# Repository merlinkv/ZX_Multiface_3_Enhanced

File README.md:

# ZX Multiface 3 Enhanced

<br />This work is licensed under a <a rel="license" href="http://creativecommons.org/licenses/by-nc-sa/4.0/">Creative Commons Attribution-NonCommercial-ShareAlike 4.0 International License</a>.

* If you remix, transform, or build upon the material, you must distribute your contributions under the same license as the original.
* You may not use the material for commercial purposes.
* You must give appropriate credit, provide a link to the license, and indicate if changes were made. You may do so in any reasonable manner, but not in any way that suggests the licensor endorses you or your use.

This interface is based on the Multiface 3 clone by Hard Micro and the recreation made by José Leandro Novellón.

# ATTENTION

   - This project was made for retro community, individuals or forums, and NOT FOR COMMERCIAL PURPOSES.
   - Its commercial sale on eBay, auction sites or shops (online or not) is PROHIBITED.
   - So only retro hardware forums and individual people with non profit intentions can build this project.

# Exception

  - If you wish to sell small quantities of this interface in a physical or online store, you must first contact me to request permission. The ban on selling it on eBay or auction sites remains in effect.

**I take no responsibiltiy for any damage to any equipment that results from the use of this board.**

USE IT AT YOUR OWN RISK!

# Version 2.0s - September 2, 2024

- Added case files of version 2.0s (STL - 3D Printer files)

# Version 2.0Ds - August 15, 2024

- New version of the board. This is an small form factor PCB but including a rear Edge connector.
- To maintain the size, the board has been designed as a four layers PCB.
- [Interactive BOM](https://htmlpreview.github.io/?https://github.com/merlinkv/ZX_Multiface_3_Enhanced/blob/main/ZX_Multiface_3_2_0Ds.html)

# Version 2.0s Final - August 6, 2024

- Version 2.0s has been tested an working 100%
- [Interactive BOM](https://htmlpreview.github.io/?https://github.com/merlinkv/ZX_Multiface_3_Enhanced/blob/main/ZX_Multiface_3_2_0s.html)

# Added version 2.0s (small) - July 04, 2024 - RC2 version, needs to be tested.

   - Redefined Kempston Joystick side (no more GAL22V10D)
   - Stay only three TH components 27E257 (ROMs), 6264/62256 (RAM) and GAL16V8B (MF3 operative) all other componentes now are SMD/SMT.
   - PCB size: 73.1 x 86.3 mm

# Versions 1.5D & 1.5DE - August 12, 2021

A better routing of the boards has been carried out and a power LED has been added.

Version 1.5DE has a rear expansion port.

# Version 1.4D - December 1, 2020

Started in April 2020, I finally got the expected results and created a fully operational and enhanced clone
of the Romantic Robot Multiface 3 for ZX Spectrum +3 computers.

The following project is a modified and improved version of the Multiface 3 interface originally designed by Romantic Robot UK LTD.
The Spanish company Hard Micro made, back in 1988, a clone of the Multiface 3. Since then there have been no more recreations that I know of.

The Multiface 3 is a multipurpose interface designed for ZX Spectrum +3 computers that, among many other functionalities,
allows us to make backup copies of programs or games on tape or disk. If used on the + 2A / + 2B models, such copies can only be made on tape.

The main changes compared to the original model are:

- Dual ROM based on a W27E257
- PAL16L8 replaced by GAL16V8B
- RAM 6264 or 62256 (best to use HM62256ALP-10).
- Tested RAM IC's:
  - HM62256ALP-10
  - HM6264LP-12
  - HY62256A LP-70
  - UT6264CPCL-70LL 
- RESET button.
- Decoupling capacitors for all IC's.
- Horizontal EDGE connector.
- PCB designed to put inside a printed 3D case.
- Kempston Joystick interface (can be enabled or disabled)

# Notes for Gotek (FlashFloppy) users:

- To format a real 3.5" disk to 720k that the ZX +3 can read (+3DOS), the best is to do it with the CPCDiskXP utility.
- These DSK files can be used as real diks to save or load MF3 snapshots.
- You must update the Gotek firmware to the latest FlashFloppy version (at the moment the v3.42).

# General Notes

- All versions, **1.4D, 1.5D, 1.5DE & 2.0s & 2.0Ds** have been tested on my ZX +3 computers and are working perfectly even with the +3e ROMs by Garry Lancaster (https://worldofspectrum.org/zxplus3e/)

# Links:

- https://www.winuaespanol.com/phpbb3/viewtopic.php?p=5981#p5981
- https://hardware.speccy.org/old.html
- https://k1.spdns.de/Vintage/Sinclair/82/Peripherals/Multiface%20I%2C%20128%2C%20and%20%2B3%20(Romantic%20Robot)/MF3/Technical%20Information/
- https://speccy4ever.speccy.org/_RR.htm

Special thanks to José Leandro, Bone and Cacharreo for their help.

# Contact

You can contact with me at the next forums:

- https://www.winuaespanol.com/phpbb3/index.php
- https://www.va-de-retro.com/foros/index.php
- http://retrowiki.es/portal

# Original introduction

MULTIFACE 3 is a multi-purpose interface designed exclusively for the
SPECTRUM+3. It provides fully automatic and universal back-up/transfer of
48/128K programs from tape to disk, disk to tape, tape to tape and disk to
disk. It also incorporates a comprehensive toolkit enabling you to
study/modify/develop software. MULTIFACE 3 can copy screens to printer in
hi-res modes and it extends the use of DOS in 48 SPECTRUM mode. MULTIFACE
is menu-driven, fully error-trapped with on-screen prompts and it largely
uses a system of one-touch commands. It is very easy to use and does not
really need a separate written manual. Nonetheless, the following few pages
should help you to understand every aspect of MULTIFACE 3 operations so that
you can use it to its fullest possible potential.

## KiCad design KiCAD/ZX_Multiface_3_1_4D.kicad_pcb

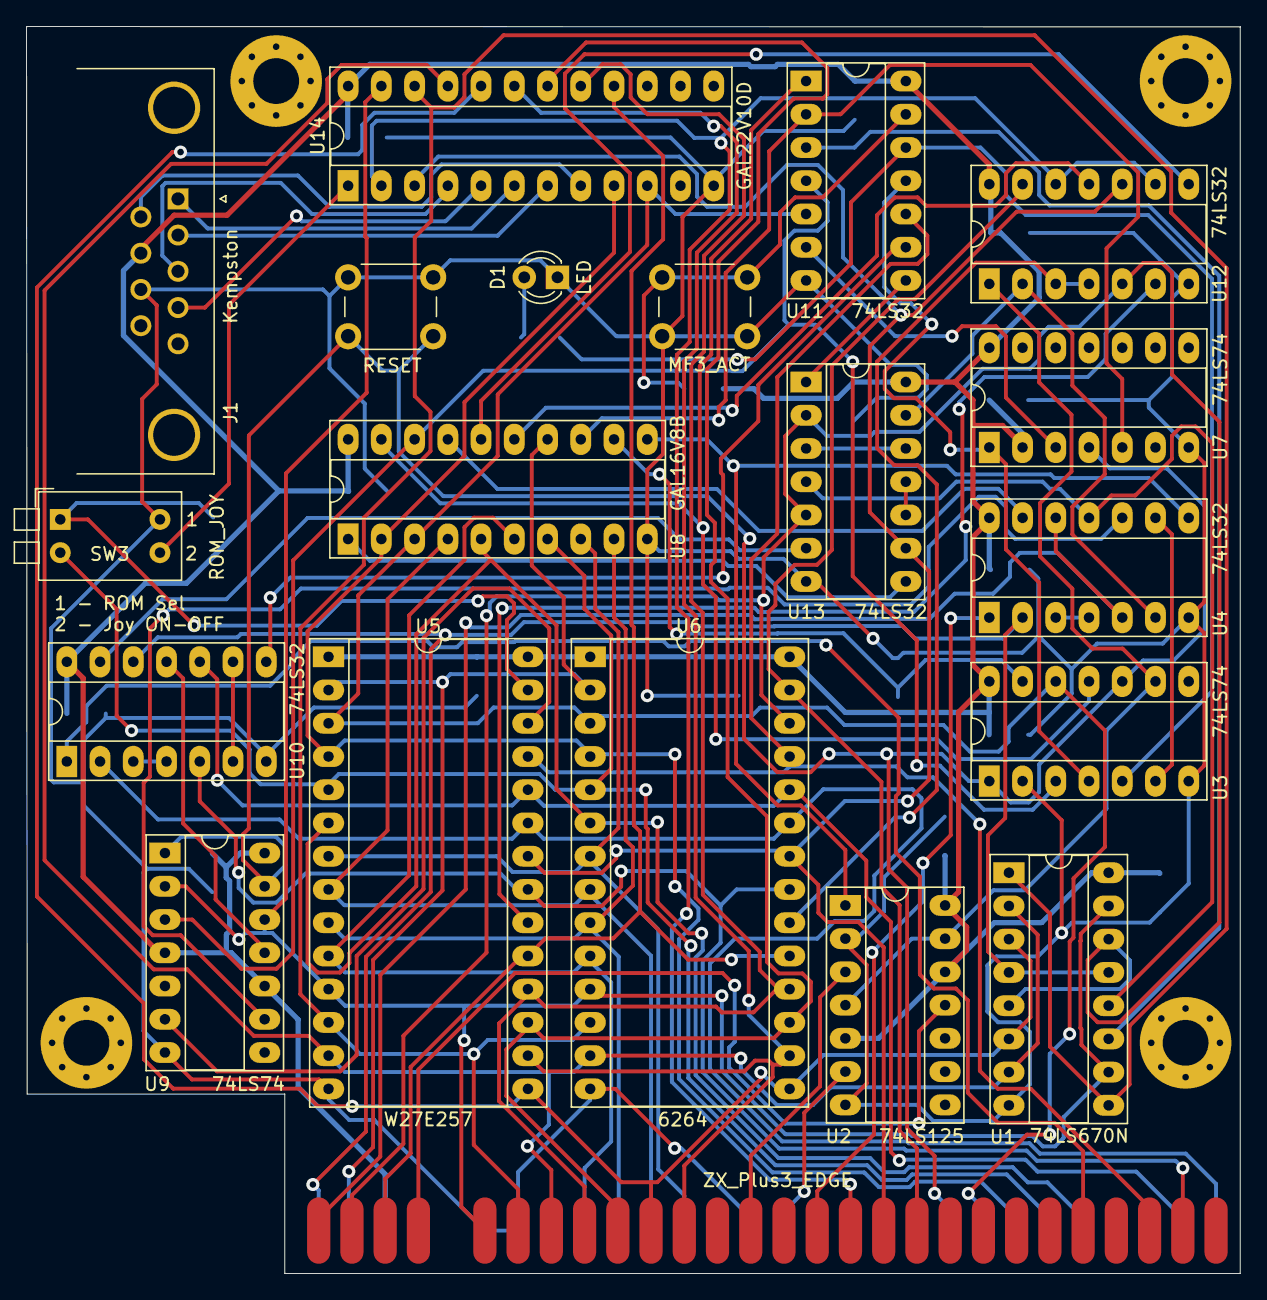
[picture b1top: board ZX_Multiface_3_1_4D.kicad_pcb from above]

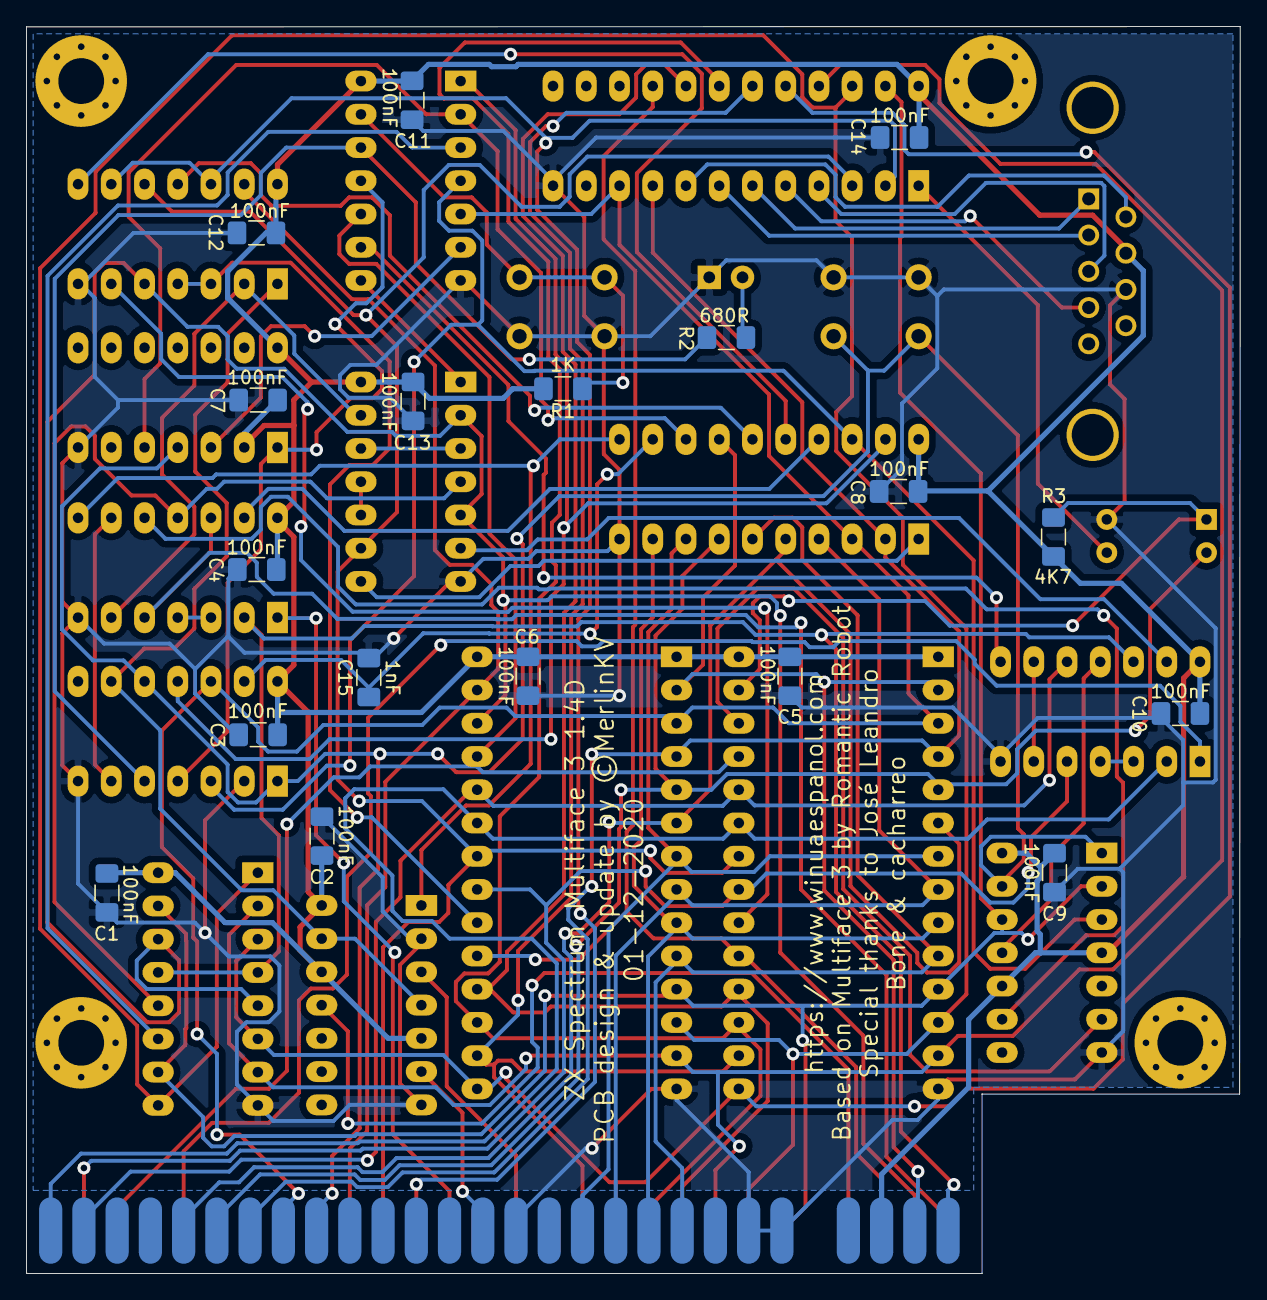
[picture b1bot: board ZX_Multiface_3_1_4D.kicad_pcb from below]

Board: 2 copper layers, 92.8 x 95.3 mm, 42 parts (18 on the bottom side), 74 nets.

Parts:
C1, C2, C3, C4, C5, C6, C7, C8, C9, C10, C11, C12, C13, C14: 100nF; C_1206_3216Metric_Pad1.42x1.75mm_HandSolder
C15: 1nF; C_1206_3216Metric_Pad1.42x1.75mm_HandSolder
CN1: ZX_Plus3_EDGE; ZX_CONNECTOR_GENERIC_SORTED
D1: LED; LED_D3.0mm
HOLE1, HOLE2, HOLE3, HOLE4: MountingHole_3.5mm_Pad_Via
J1: Kempston; DSUB-9_Male_Horizontal_P2.77x2.84mm_EdgePinOffset4.94mm_Hou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
R1: 1K; R_1206_3216Metric_Pad1.42x1.75mm_HandSolder
R2: 680R; R_1206_3216Metric_Pad1.42x1.75mm_HandSolder
R3: 4K7; R_1206_3216Metric_Pad1.42x1.75mm_HandSolder
SW1: RESET; SW_PUSH_6mm_H13mm
SW2: MF3_ACT; SW_PUSH_6mm_H13mm
SW3: ROM_JOY; SW_DIP_SPSTx02_Piano_10.8x6.64mm_W7.62mm_P2.54mm
U1: 74LS670N; DIP-16_W7.62mm_Socket_LongPads
U2: 74LS125; DIP-14_W7.62mm_Socket_LongPads
U3, U7, U9: 74LS74; DIP-14_W7.62mm_Socket_LongPads
U4, U10, U11, U12, U13: 74LS32; DIP-14_W7.62mm_Socket_LongPads
U5: W27E257; DIP-28_W15.24mm_Socket_LongPads
U6: 6264; DIP-28_W15.24mm_Socket_LongPads
U8: GAL16V8B; DIP-20_W7.62mm_Socket_LongPads
U14: GAL22V10D; DIP-24_W7.62mm_Socket_LongPads

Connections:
+5V: C1.2, C2.2, C3.2, C4.2, C5.2, C6.2, C7.2, C8.2, C9.2, C10.2, C11.2, C12.2, C13.2, C14.2, CN1.3B, J1.7, R1.1, R3.1, U1.16, U2.5, U2.12, U2.14, U3.14, U4.14, U5.1, U5.28, U6.1, U6.28, U7.2, U7.14, U8.20, U9.4, U9.10, U9.14, U10.14, U11.14, U12.14, U13.14, U14.24
/A13a: U5.26, U9.6
A0: CN1.9B, U5.10, U6.10, U8.6
A1: CN1.10B, U5.9, U6.9, U8.9
A2: CN1.11B, U5.8, U6.8, U8.4
A3: CN1.12B, U5.7, U6.7, U8.8
A4: CN1.24B, U5.6, U6.6, U8.5
A5: CN1.23B, SW3.2, U5.5, U6.5, U8.7
A6: CN1.22B, U5.4, U6.4, U8.2, U14.9
A7: CN1.21B, U3.12, U5.3, U6.3, U8.3, U11.5, U14.10
A8: CN1.26A, U5.25, U6.25, U11.10
A9: CN1.27B, U5.24, U6.24, U10.10
A10: CN1.27A, U5.21, U6.21, U10.5
A11: CN1.28B, U5.23, U6.23, U10.2
A12: CN1.2B, U5.2, U6.2, U8.14
A13: CN1.2A, U1.5, U1.14, U6.26, U12.5, U13.2, U13.5
A14: CN1.1B, U1.4, U1.13, U4.2, U10.12
A15: CN1.1A, U4.5, U4.12
D0: CN1.6A, U1.10, U1.15, U5.11, U6.11, U9.2, U9.12, U14.23
D1: CN1.7A, U1.1, U1.9, U5.12, U6.12, U14.22
D2: CN1.8A, U1.2, U1.7, U5.13, U6.13, U14.21
D3: CN1.11A, U1.3, U1.6, U5.15, U6.15, U14.20
D4: CN1.12A, U5.16, U6.16, U14.19
D5: CN1.10A, U5.17, U6.17, U14.18
D6: CN1.9A, U5.18, U6.18, U14.17
D7: CN1.3A, U5.19, U6.19, U14.16
GND: C1.1, C2.1, C3.1, C4.1, C5.1, C6.1, C7.1, C8.1, C9.1, C10.1, C11.1, C12.1, C13.1, C14.1, C15.2, CN1.6B, CN1.7B, CN1.14B, D1.1, J1.8, SW1.1, SW2.2, SW3.4, U1.8, U2.2, U2.7, U3.2, U3.7, U4.7, U5.14, U6.14, U7.7, U8.10, U9.7, U10.7, U11.7, U12.7, U13.7, U14.12
IORQ: CN1.17A, U12.9, U12.12, U14.2
J1_UP: J1.1, U14.6
J2_DOWN: J1.2, U14.7
J3_LEFT: J1.3, U14.4
J4_RIGHT: J1.4, U14.5
J6_FIRE: J1.6, U14.8
JOY_EN: SW3.3, U14.1
M1: CN1.24A, U10.1
MREQ: CN1.16A, U4.1
NMI: CN1.14A, U2.3
unnamed: C15.1, U3.13, U8.12
unnamed: D1.2, R2.1
unnamed: R1.2, SW2.1, U11.13
unnamed: R2.2, U3.5, U11.12
unnamed: U1.11, U11.3
unnamed: U1.12, U4.11, U13.4
unnamed: U2.1, U4.8, U8.11
unnamed: U3.6, U4.9
unnamed: U4.3, U4.4
unnamed: U4.10, U9.9
unnamed: U4.13, U8.17
unnamed: U10.3, U10.4
unnamed: U10.6, U10.9
unnamed: U10.8, U11.9
unnamed: U9.11, U10.11
unnamed: U10.13, U13.6
unnamed: U3.11, U8.19, U11.1
unnamed: U7.5, U8.13, U11.2
unnamed: U3.3, U8.18, U9.3, U11.4
unnamed: U7.3, U11.6
unnamed: U11.8, U13.1
unnamed: U3.4, U7.1, U11.11
unnamed: U2.4, U2.13, U3.9, U12.1
unnamed: U4.6, U12.2, U13.13
unnamed: U6.20, U12.3, U12.4
unnamed: U5.20, U12.6
unnamed: U8.16, U12.8
unnamed: U8.15, U12.11
unnamed: U8.1, U13.8
unnamed: U13.10, U13.11
unnamed: U13.3, U13.12
RD: CN1.18A, U5.22, U6.22, U12.10, U13.9, U14.3
RESET: CN1.20B, SW1.2, U3.1, U3.10, U7.4, U9.1, U9.13
ROM1_OE: CN1.4A, U2.11
ROM2_OE: CN1.15B, U2.6
ROMS1: R3.2, SW3.1, U5.27
WR: CN1.19A, U6.27, U12.13

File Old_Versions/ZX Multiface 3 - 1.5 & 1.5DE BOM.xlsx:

Id | Designator | Package | Quantity | Designation | Supplier and ref
1 | U14 | DIP-24_W7.62mm_Socket | 1 | GAL22V10D
2 | U13,U12,U11,U10,U4 | DIP-14_W7.62mm_Socket | 5 | 74LS32
3 | U9,U7,U3 | DIP-14_W7.62mm_Socket | 3 | 74LS74
4 | U8 | DIP-20_W7.62mm_Socket | 1 | GAL16V8B
5 | U6 | DIP-28_W15.24mm_Socket | 1 | 6264 / 62256
6 | U5 | DIP-28_W15.24mm_Socket | 1 | W27E257
7 | U2 | DIP-14_W7.62mm_Socket | 1 | 74LS125
8 | U1 | DIP-16_W7.62mm_Socket | 1 | 74LS670N
9 | CN2 | ZX_EDGE_BACK | 1 | ZX_Plus3_BACK
10 | CN1 | ZX_EDGE_SOLDER | 1 | ZX_Plus3_SOLDER
11 | R4,R2 | R_1206_3216Metric_Pad1.42x1.75mm_HandSolder | 2 | 680R
12 | D2 | LED_D3.0mm | 1 | PWR_LED
13 | C14,C13,C12,C11,C10,C9,C8,C7,C6,C5,C4,C3,C2,C1 | C_1206_3216Metric_Pad1.42x1.75mm_HandSolder | 14 | 100nF
14 | SW3 | SW_DIP_SPSTx02_Piano_10.8x6.64mm_W7.62mm_P2.54mm | 1 | ROM_JOY
15 | J1 | DSUB-9_Male_Horizontal_P2.77x2.84mm_EdgePinOffset4.94mm_Housed_MountingHolesOff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 | 1 | Kempston
16 | R3 | R_1206_3216Metric_Pad1.42x1.75mm_HandSolder | 1 | 4K7
17 | R1 | R_1206_3216Metric_Pad1.42x1.75mm_HandSolder | 1 | 1K
18 | SW2 | SW_PUSH_6mm_H13mm | 1 | MF3_ACT
19 | SW1 | SW_PUSH_6mm_H13mm | 1 | RESET
20 | C15 | C_1206_3216Metric_Pad1.42x1.75mm_HandSolder | 1 | 1nF
21 | HOLE4,HOLE2,HOLE1,HOLE3 | MountingHole_3.5mm_Pad_Via | 4 | MountingHole_3.5mm_Pad_Via
22 | D1 | LED_D3.0mm | 1 | MF_LED

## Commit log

2020-12-02 Create aa
2024-06-26 Create aaa

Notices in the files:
KiCAD/ZX_Multiface_3_1_4D.kicad_pcb:
PCB design & update by ©MerlinKV
